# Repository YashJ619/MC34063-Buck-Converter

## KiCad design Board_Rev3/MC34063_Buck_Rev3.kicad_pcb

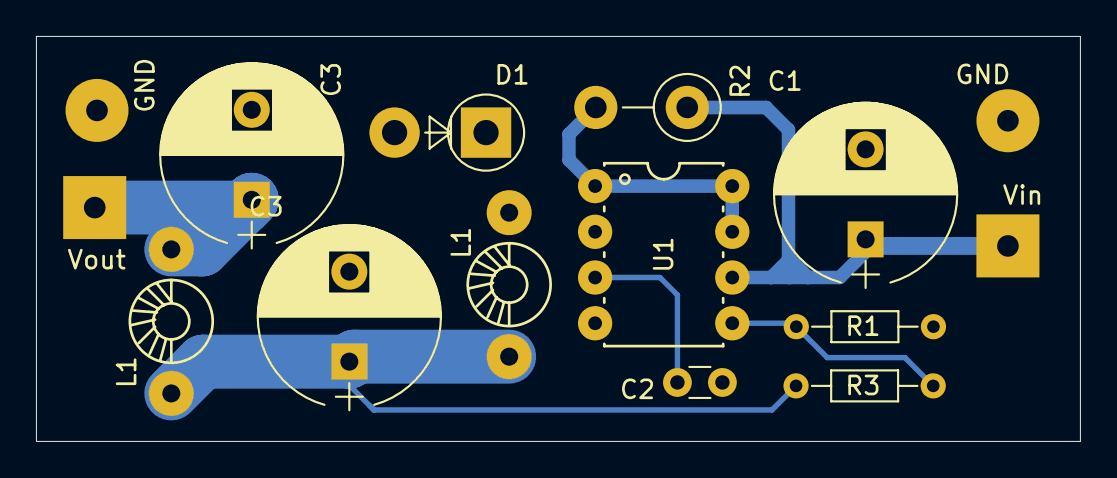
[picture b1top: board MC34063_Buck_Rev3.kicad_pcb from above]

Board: 2 copper layers, 58.0 x 22.5 mm, 15 parts (0 on the bottom side), 7 nets.

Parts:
C1: 100uF25v; CP_Radial_D10.0mm_P5.00mm
C2: 470pF; C_Disc_D3.0mm_W1.6mm_P2.50mm
C3, C3#2: 470uF25v; CP_Radial_D10.0mm_P5.00mm
D1: 1N5819; D_5W_P5.08mm_Vertical_AnodeUp
GND: SolderWirePad_single_1-2mmDrill
GND#2: SolderWirePad_single_1-2mmDrill
L1, L1#2: 150uH; Choke_Toroid_horizontal_Diameter4-5mm_Amidon-T16
R1: 1.2K; R_Axial_DIN0204_L3.6mm_D1.6mm_P7.62mm_Horizontal
R2: 0R2 1/2W; R_Axial_DIN0411_L9.9mm_D3.6mm_P5.08mm_Vertical
R3: 3.6K; R_Axial_DIN0204_L3.6mm_D1.6mm_P7.62mm_Horizontal
U1: MC34063AP; PDIP-8
Vin: SolderWirePad_single_1-2mmDrill
Vout: SolderWirePad_single_1-2mmDrill

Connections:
GNDREF: C1.2, C2.2, C3.2, C3#2.2, D1.2, GND.1, GND#2.1, R1.2, U1.4
unnamed: C2.1, U1.3
unnamed: D1.1, L1.1, U1.2
unnamed: R1.1, R3.1, U1.5
unnamed: R2.2, U1.1, U1.7, U1.8
VCC: C1.1, R2.1, U1.6, Vin.1
Vout1: C3.1, L1.2, L1#2.2, R3.2

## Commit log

2022-11-19 Created board Rev1
2022-11-19 Created Board Rev2
2022-11-19 Created Board Rev3
2022-11-19 Created panel for all 4 designs and gerber files for all boards
2022-11-20 Images added for all Boards and schemetics
2022-11-20 Datasheets and other documents added
2022-11-20 Excel file added for direct calculation of buck convertor
